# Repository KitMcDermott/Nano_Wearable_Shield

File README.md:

IDM Nano Wearable Shield License info
============================

This design is a wearable shield for an Arduino Nano, operating at 3.3V. 
https://idmwearables.club/ 

This design is based on an original design by Sparkfun, for a Photon. https://learn.sparkfun.com/tutorials/photon-wearable-shield-hookup-guide- 
https://github.com/sparkfun/Photon_Wearable_Shield 

License Information
-------------------
This product is open source! 

The hardware is released under [Creative Commons ShareAlike 4.0 International](https://creativecommons.org/licenses/by-sa/4.0/).

Please use, reuse, and modify these files as you see fit. Please maintain attribution to SparkFun Electronics and release anything derivative under the same license.

Distributed as-is; no warranty is given.

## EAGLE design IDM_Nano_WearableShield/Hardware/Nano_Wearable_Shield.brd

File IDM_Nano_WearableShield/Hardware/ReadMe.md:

IDM Nano Wearable Shield License info
============================

This design is a wearable shield for an Arduino Nano, operating at 3.3V. 
https://idmwearables.club/ 

This design is based on an original design by Sparkfun, for a Photon. https://learn.sparkfun.com/tutorials/photon-wearable-shield-hookup-guide- 
https://github.com/sparkfun/Photon_Wearable_Shield 

License Information
-------------------
This product is open source! 

The hardware is released under [Creative Commons ShareAlike 4.0 International](https://creativecommons.org/licenses/by-sa/4.0/).

Please use, reuse, and modify these files as you see fit. Please maintain attribution to SparkFun Electronics and release anything derivative under the same license.

Distributed as-is; no warranty is given.

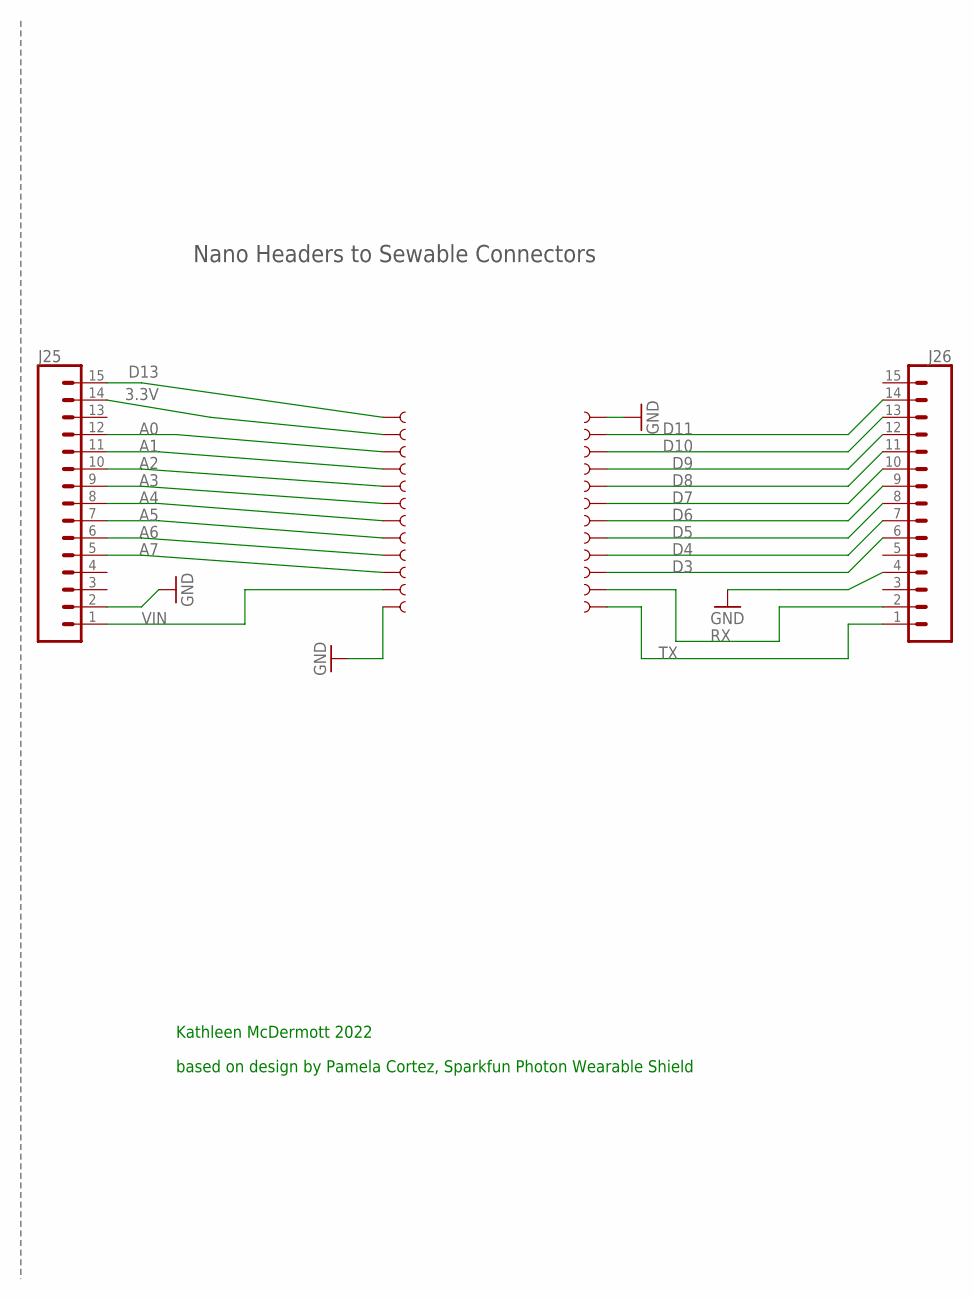
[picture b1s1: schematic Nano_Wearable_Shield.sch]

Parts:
J1, J2, J3, J4, J5, J6, J7, J8, J9, J10, J11, J12, J13, J14, J15, J16, J17, J18, J19, J20, J21, J22, J23, J24: PAD; PAD-LONG-2-SIDED
J25, J26: CONN_15; 1X15

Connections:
3.3V: J2.1, J25.14
A0: J3.1, J25.12
A1: J4.1, J25.11
A2: J5.1, J25.10
A3: J6.1, J25.9
A4: J7.1, J25.8
A5: J8.1, J25.7
A6: J9.1, J25.6
A7: J10.1, J25.5
D3: J22.1, J26.6
D4: J21.1, J26.7
D5: J20.1, J26.8
D6: J19.1, J26.9
D7: J18.1, J26.10
D8: J17.1, J26.11
D9: J16.1, J26.12
D10: J15.1, J26.13
D11: J14.1, J26.14
D13: J1.1, J25.15
GND: J12.1, J13.1, J25.2, J26.4
RX: J23.1, J26.2
TX: J24.1, J26.1
VIN: J11.1, J25.1

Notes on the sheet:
Nano Headers to Sewable Connectors
Kathleen McDermott 2022
based on design by Pamela Cortez, Sparkfun Photon Wearable Shield

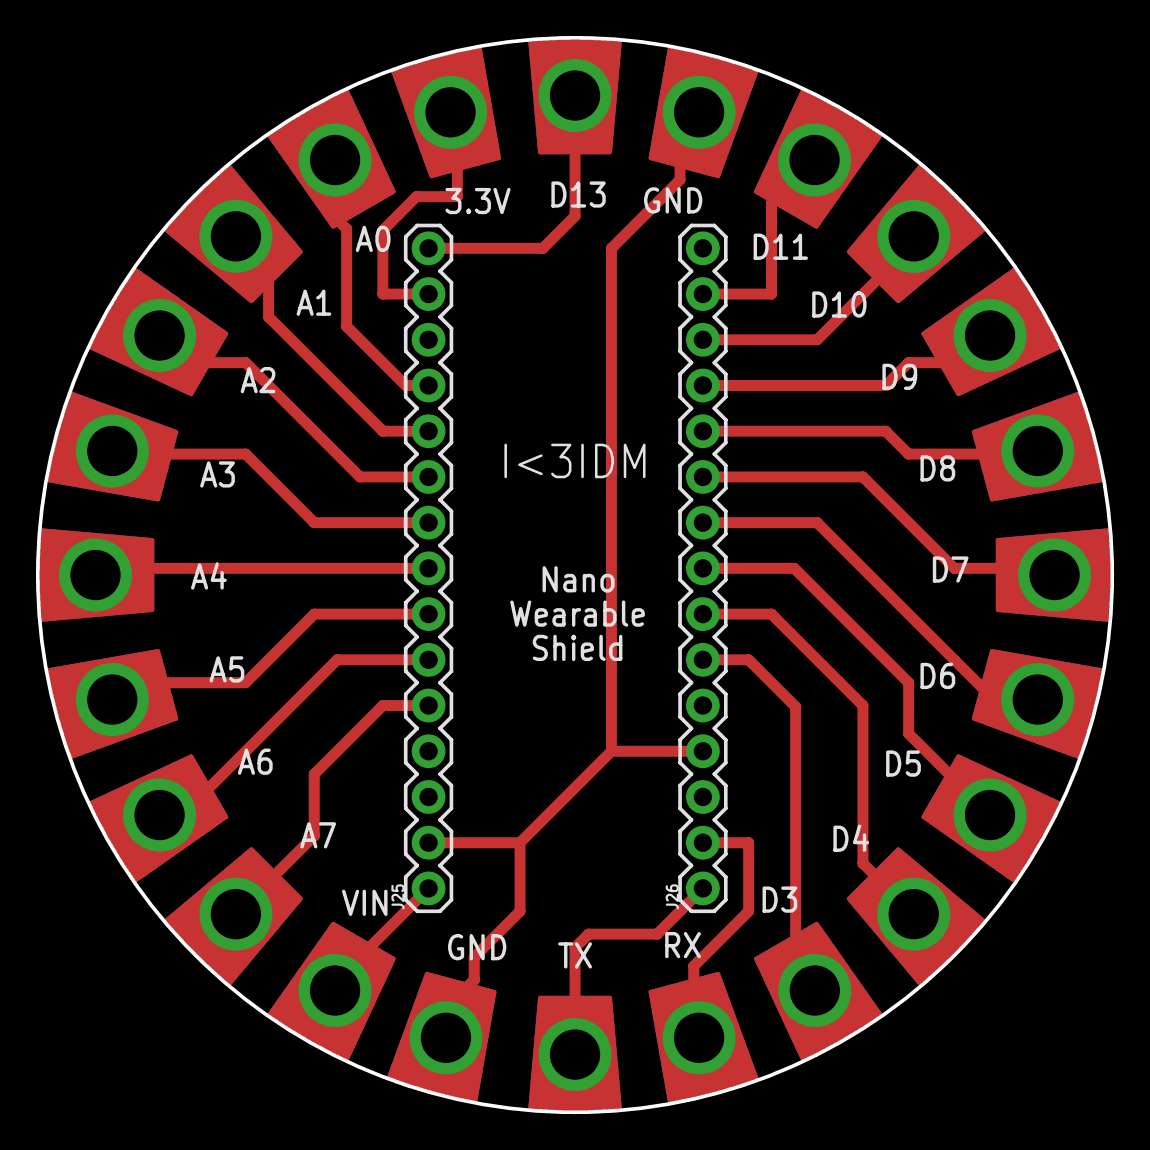
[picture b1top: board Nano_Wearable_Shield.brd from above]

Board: 2 copper layers, 59.7 x 59.7 mm, 26 parts (0 on the bottom side), 23 nets.

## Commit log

2022-01-04 Rename IDM_Nano_WearableShield/ReadMe.md to README.md
2022-01-04 Add original Photon shield design files
2022-01-04 Update ReadMe.md
    Nano Shield

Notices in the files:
parts and their libraries:
Photon_wearable: Licensing:Creative Commons ShareAlike 4.0 International - https://creativecommons.org/licenses/by-sa/4.0
